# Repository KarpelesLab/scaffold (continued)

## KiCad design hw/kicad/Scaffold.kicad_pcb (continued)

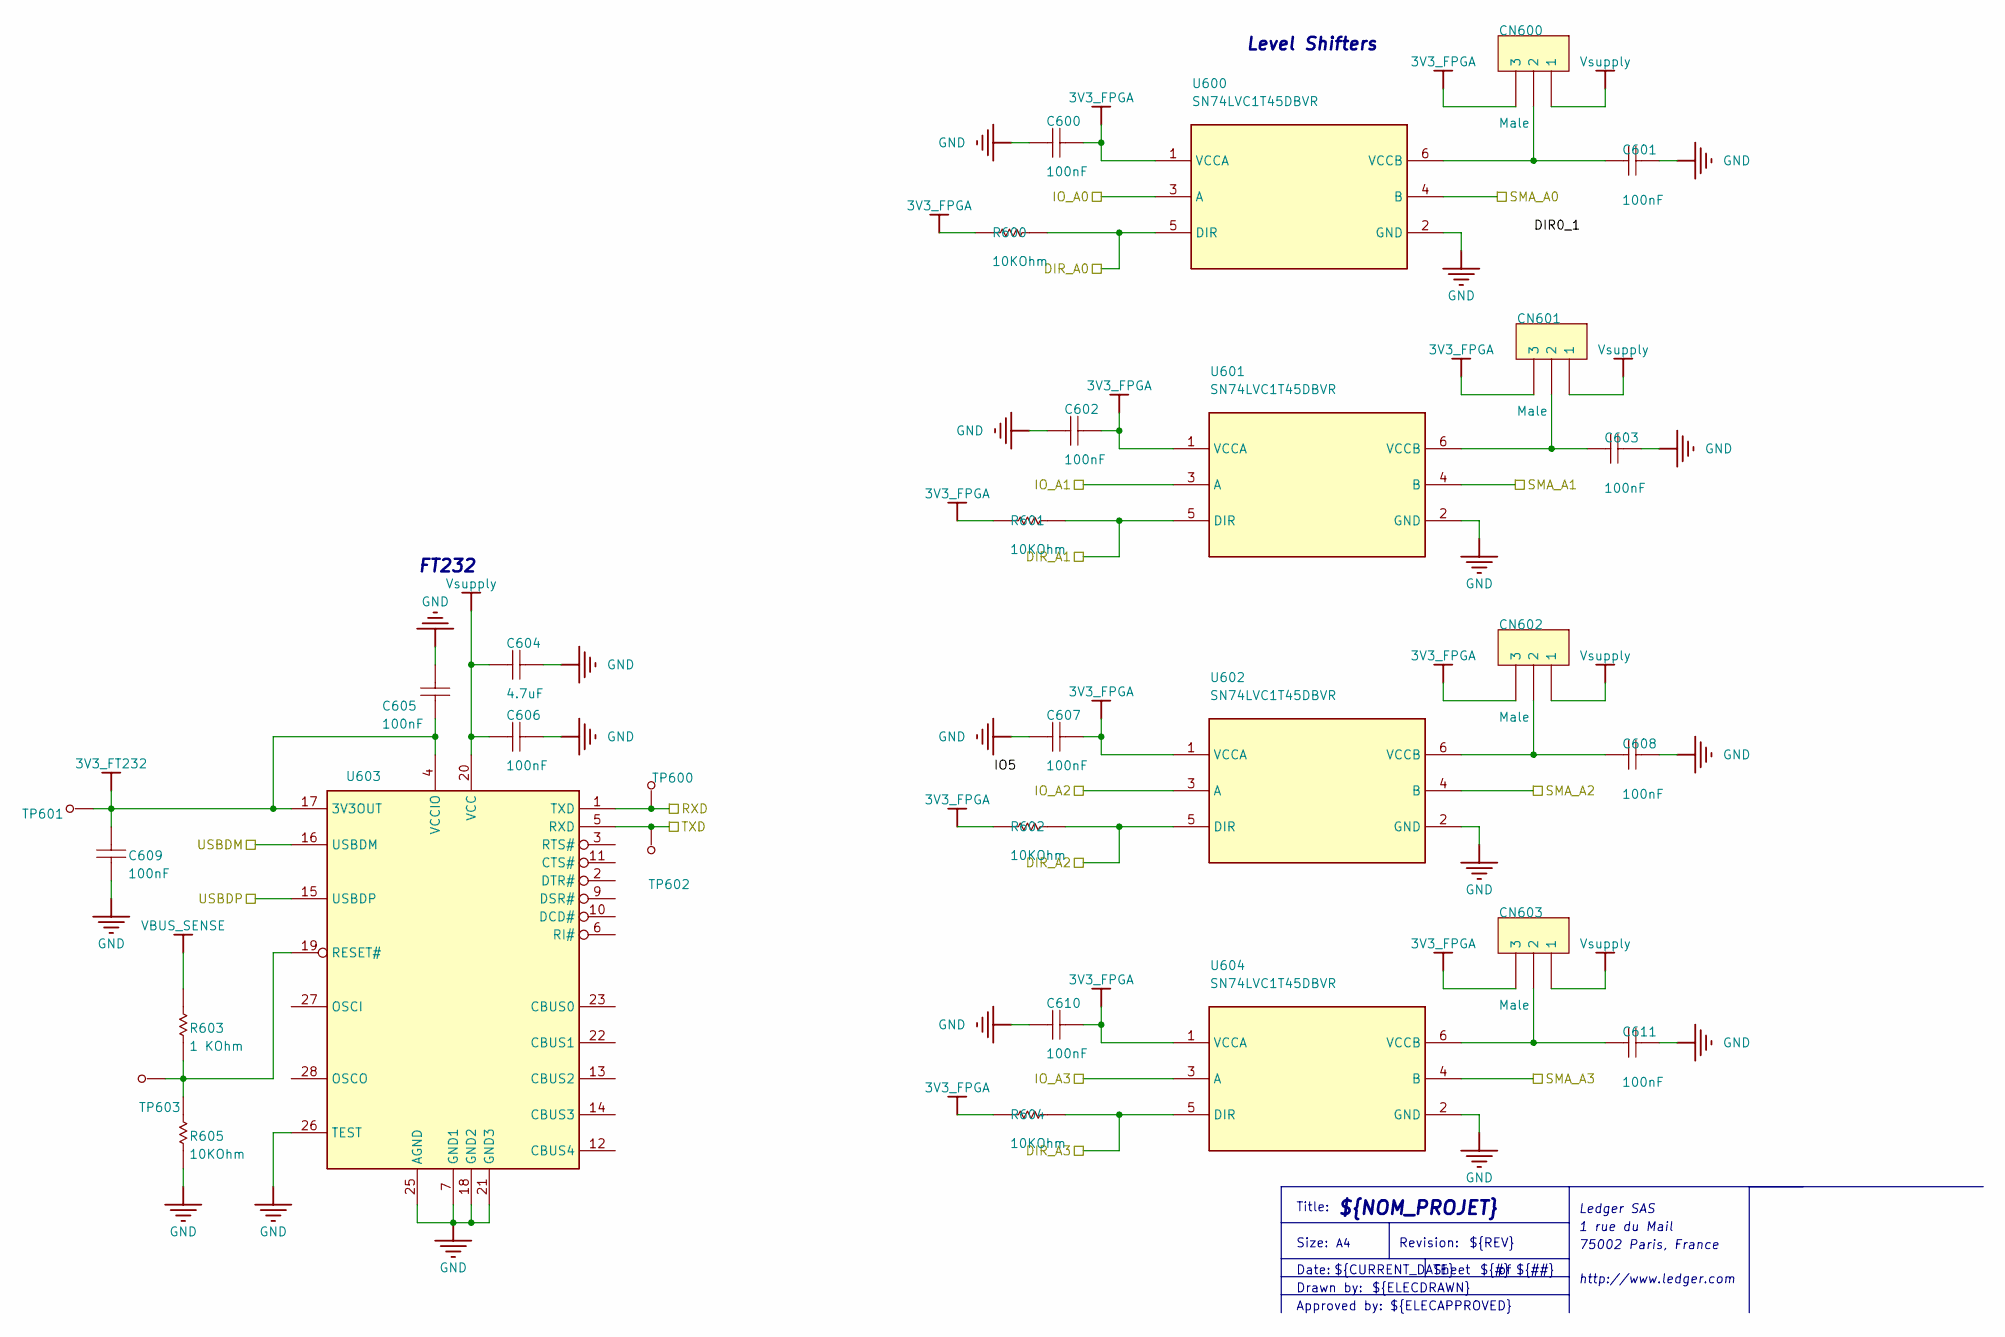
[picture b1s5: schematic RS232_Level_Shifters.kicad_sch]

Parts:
C600, C601, C602, C603, C605, C607, C608, C609, C610, C611: 100nF; CAP0603; TOLERANCE 10%; MANUFACTURER2 PN MCCA000159
C604: 4.7uF; CAP0603; TOLERANCE 10%; MANUFACTURER PN GRM188R61C475KE11
C606: 100nF; CAP0603; TOLERANCE 10%; MANUFACTURER PN 885012206046
CN600, CN601, CN602, CN603: Male; MOLEX_90120-0123; MANUFACTURER PN 90120-0123
R600, R601, R602, R604, R605: 10KOhm; RES0603; TOLERANCE 1%; MANUFACTURER PN RC0603FR-0710KL
R603: 1 KOhm; RES0603; TOLERANCE 1%; MANUFACTURER PN 0603WAF1001T5E
TP600, TP601, TP602, TP603: TP; TP_001
U600, U601, U602, U604: SN74LVC1T45DBVR; SOT95P280X145-6N; MANUFACTURER PN SN74LVC1T45DBVR
U603: IC - USB-to-UART 1-CH 256Byte FIFO - 5V - 28-Pin 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; SSOP28DB; MANUFACTURER PN FT232RL

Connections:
3V3_FPGA: C600.2, C602.2, C607.2, C610.2, CN600.3, CN601.3, CN602.3, CN603.3, R600.2, R601.2, R602.2, R604.2, U600.1 (VCCA), U601.1 (VCCA), U602.1 (VCCA), U604.1 (VCCA); also elsewhere on the board
3V3_FT232: C605.1, C609.1, TP601.1, U603.4 (VCCIO), U603.17 (3V3OUT)
/USBDM: U603.16 (USBDM); also elsewhere on the board
/USBDP: U603.15 (USBDP); also elsewhere on the board
/U_Connectors/IO_SMA0: U600.4 (B); also elsewhere on the board
/U_Connectors/IO_SMA1: U601.4 (B); also elsewhere on the board
/U_Connectors/IO_SMA2: U602.4 (B); also elsewhere on the board
/U_Connectors/IO_SMA3: U604.4 (B); also elsewhere on the board
/U_FPGA/DIR_A0: R600.1, U600.5 (DIR); also elsewhere on the board
/U_FPGA/DIR_A1: R601.1, U601.5 (DIR); also elsewhere on the board
/U_FPGA/DIR_A2: R602.1, U602.5 (DIR); also elsewhere on the board
/U_FPGA/DIR_A3: R604.1, U604.5 (DIR); also elsewhere on the board
/U_FPGA/IO_A0: U600.3 (A); also elsewhere on the board
/U_FPGA/IO_A1: U601.3 (A); also elsewhere on the board
/U_FPGA/IO_A2: U602.3 (A); also elsewhere on the board
/U_FPGA/IO_A3: U604.3 (A); also elsewhere on the board
/U_FPGA/RXD: TP600.1, U603.1 (TXD); also elsewhere on the board
/U_FPGA/TXD: TP602.1, U603.5 (RXD); also elsewhere on the board
GND: C600.1, C601.1, C602.1, C603.1, C604.2, C605.2, C606.2, C607.1, C608.1, C609.2, C610.1, C611.1, R605.1, U600.2 (GND), U601.2 (GND), U602.2 (GND), U603.7 (GND1), U603.18 (GND2), U603.21 (GND3), U603.25 (AGND), U603.26 (TEST), U604.2 (GND); also elsewhere on the board
unnamed: C601.2, CN600.2, U600.6 (VCCB)
unnamed: C603.2, CN601.2, U601.6 (VCCB)
unnamed: C608.2, CN602.2, U602.6 (VCCB)
unnamed: R603.1, R605.2, TP603.1, U603.19 (RESET#)
unnamed: C611.2, CN603.2, U604.6 (VCCB)
VBUS_SENSE: R603.2; also elsewhere on the board
Vsupply: C604.1, C606.1, CN600.1, CN601.1, CN602.1, CN603.1, U603.20 (VCC); also elsewhere on the board

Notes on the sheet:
Sheet
Title:
Approved by:
Drawn by:
Revision:
Date:
${CURRENT_DATE}
${#}
Ledger SAS
${REV}
Size:
${NOM_PROJET}
75002 Paris, France
${ELECAPPROVED}
FT232
${##}
http://www.ledger.com
1 rue du Mail
Level Shifters
${ELECDRAWN}

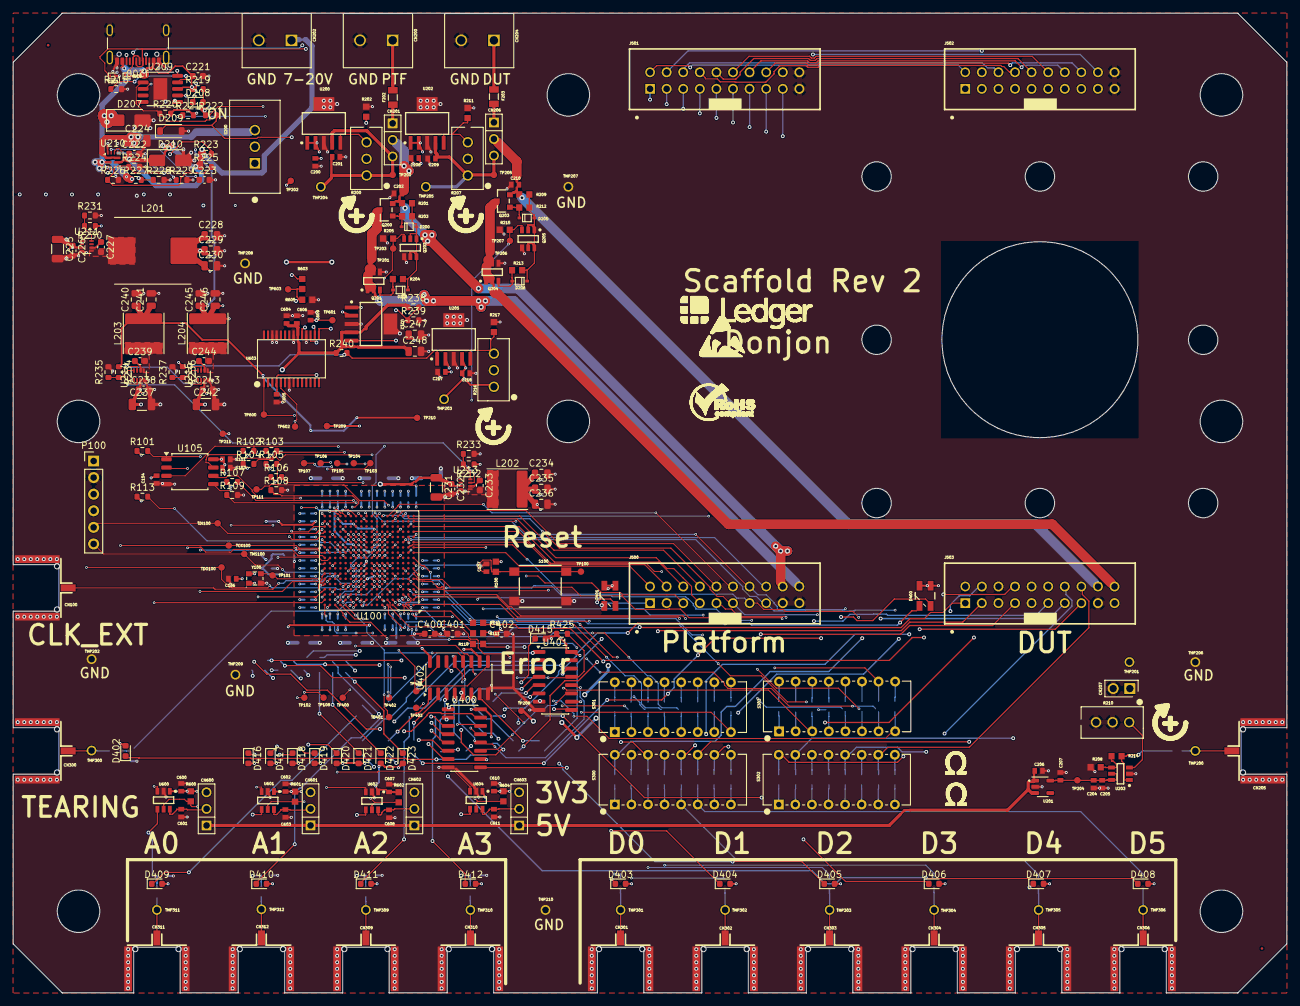
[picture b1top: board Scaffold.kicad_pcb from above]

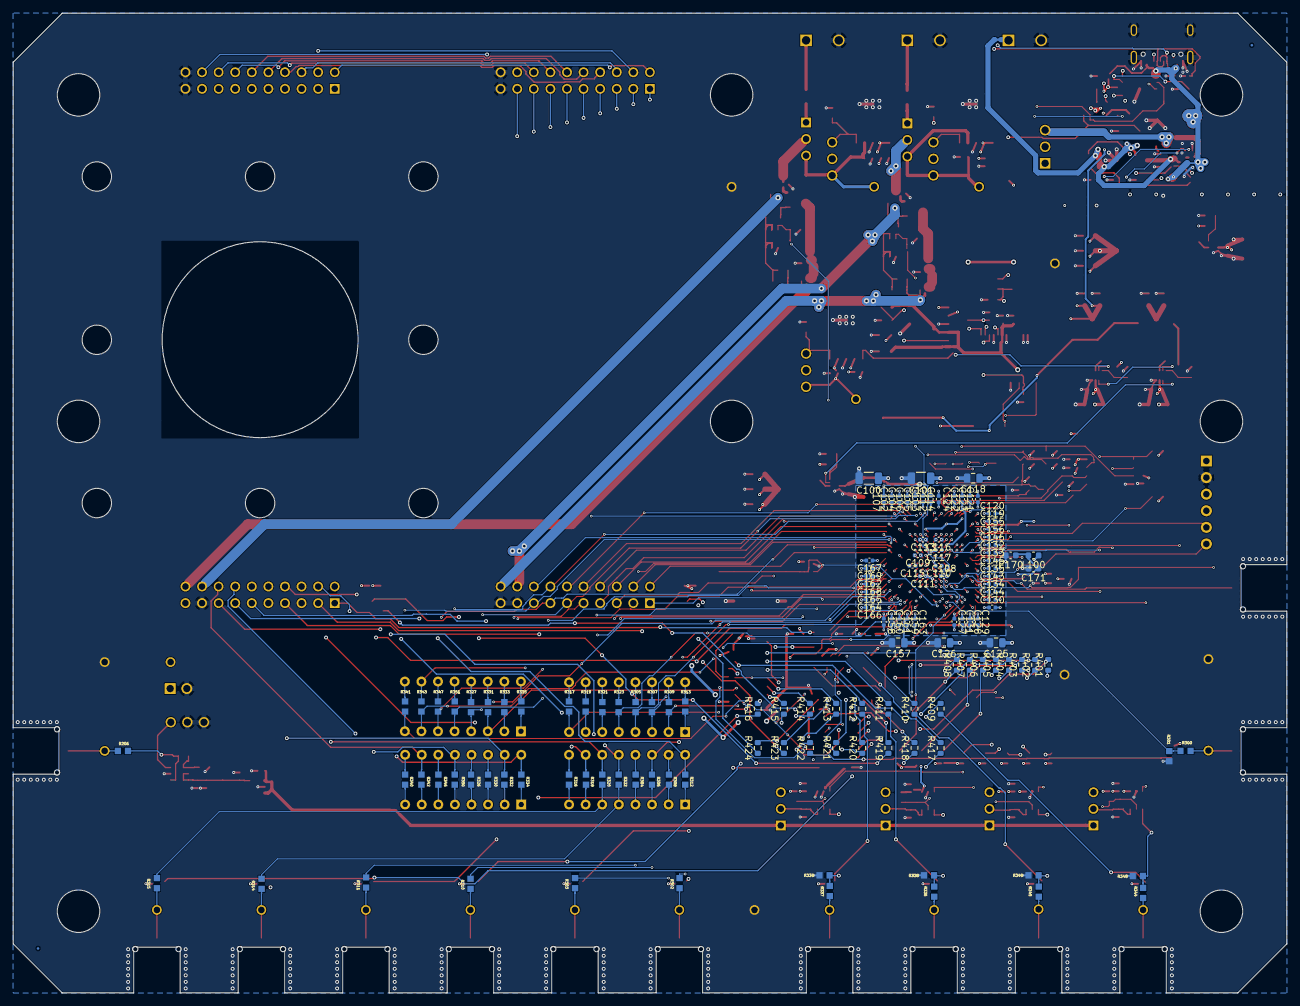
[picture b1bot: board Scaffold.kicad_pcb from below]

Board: 6 copper layers, 195.0 x 150.0 mm, 422 parts (133 on the bottom side), 252 nets.

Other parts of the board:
Logo1: Logo Ledger; logo_Ledger_new - Horizontale
Logo2: Logo ESD; LOGO ESD
Logo3: Logo ROHS
M1, M2, M3, M4: Mire; MIRE

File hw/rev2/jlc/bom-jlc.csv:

Comment,Designator,Footprint,LCSC
100uF 6.3V,"C100,C101",C_1206_3216Metric,C15008
4.7uF 10V,"C102,C103,C104,C105,C106,C107,C119,C120,C127,C128,C129,C130,C131,C158,C159,C160,C161",C_0402_1005Metric,C23733
470nF 10V,"C108,C109,C110,C111,C112,C113,C114,C115,C116,C117,C121,C122,C123,C124,C132,C133,C134,C135,C143,C144,C145,C146,C155,C156,C162,C163,C164,C165,C166,C167,C168,C169",C_0402_1005Metric,C47339
47uF 6.3V,"C118,C125,C126,C157",C_0805_2012Metric,C16780
100nF,"C136,C151,C153,C154,C205,C600,C601,C602,C603,C605,C606,C607,C608,C609,C610,C611",CAP0603,C14663
10uF,"C137,C200,C201,C202,C204,C208,C209,C210,C217,C218",CAP0603,C86277
1uF 50V,"C170,C221,C222",C_0603_1608Metric,C15849
100nF 50V,"C171,C226,C227,C232,C233,C238,C239,C243,C244,C400,C401,C402",C_0603_1608Metric,C14663
1uF,"C206,C207",CAP0603,C15849
10nF 50V,C223,C_0603_1608Metric,C57112
10uF 50V,"C224,C225,C231,C237,C242",C_1206_3216Metric,C13585
22uF 25V,"C228,C229,C230,C234,C235,C236,C240,C241,C245,C246",C_0805_2012Metric,C45783
10uF 25V,"C247,C248",C_0805_2012Metric,C15850
4.7uF,C604,CAP0603,C19666
Male,CN207,MOLEX_90120-0122,C3336192
BAT60J,"D200,D201,D205,D206",SOD323_A,C133103
ESDAXLC6-1BT2,"D203,D204",SOD882,C154523
SMAJ20A,"D207,D210",D_SMA,C115250
PD 12V OK (red),D208,LED_0603_1608Metric,C2286
BZT52C4V7,D209,D_SOD-123,C2116
LED RG,"D400,D401",PLCC-4_3528,C5872444
KT-0603Y,"D402,D403,D404,D405,D406,D407,D408,D409,D410,D411,D412,D416,D417,D418,D419,D420,D421,D422,D423",LED_0603_1608Metric,C2287
KT-0603R,D415,LED_0603_1608Metric,C2286
PTC - 1A - 0.5A - 6VDC,"F202,F203",FUSE_0805,C5220829
USB4105-GF-A,J200,USB_C_Receptacle_GCT_USB4105-xx-A_16P_TopMnt_Horizontal,C3020560
600R@100MHz,L100,L_0603_1608Metric,C1002
10uH,L201,L_CJiang_FXL1040,C475915
3.3uH,L202,L_Changjiang_FNR6045S,C168063
4.7uH,L203,L_Changjiang_FNR6045S,C168067
10uH,L204,L_Changjiang_FNR6045S,C168076
JTAG,P100,PinHeader_1x06_P2.54mm_Vertical,C492405
STR2P3LLH6 - SOT23,"Q200,Q203",SOT23,C3040112
STT6N3LLH6 - SOT23-6,"Q201,Q202,Q204,Q205",SOT95P280X145-6N,C3021100
47KOhm,R100,RES0603,C25819
10k,"R101,R102,R103,R220,R221,R224,R226,R228,R233,R425",R_0603_1608Metric,C25804
4.7k,"R104,R105,R222,R231",R_0603_1608Metric,C23162
330,"R106,R419,R420,R423,R424",R_0603_1608Metric,C23138
1k,"R107,R108,R109,R113",R_0603_1608Metric,C21190
10KOhm,"R110,R111,R112,R301,R305,R307,R309,R313,R317,R319,R321,R323,R327,R331,R333,R335,R338,R339,R341,R343,R347,R348,R349,R351,R600,R601,R602,R604,R605",RES0603,C25804
50 kOhms,"R200,R207,R216",POT_3296W,C83686
470Ohm,"R201,R209",RES0603,C23179
15KOhm,"R202,R211",RES0603,C22809
2Ohm,"R203,R204,R212,R213",RES0603,C22977
1K,"R205,R214,R215,R304,R306,R308,R312,R316,R318,R320,R322,R326,R330,R332,R334,R340,R342,R346,R350",RES0603,C21190
50 Ohm,R206,RES0603,C23185
100Ohm,R208,RES0603,C22775
100 Ohms,R210,POT_3296W,C83688
28KOhm,R217,RES0603,C22989
24k,R218,R_0603_1608Metric,C23352
2.2k,R219,R_0603_1608Metric,C4190
51k,R223,R_0603_1608Metric,C23196
200k,"R225,R227",R_0603_1608Metric,C25811
22k,R229,R_0603_1608Metric,C31850
30k,R230,R_0603_1608Metric,C22984
2.4k,R232,R_0603_1608Metric,C22940
15k,"R234,R237,R239",R_0603_1608Metric,C22809
12k,R235,R_0603_1608Metric,C22790
47k,"R236,R238",R_0603_1608Metric,C25819
100k,R240,R_0603_1608Metric,C25803
0 Ohm,"R300,R302,R303,R310,R311,R314,R315,R336,R337,R344,R345",RES0603,C21189
680,"R401,R402,R403,R404,R405,R406,R407,R408,R409,R410,R411,R412,R413,R414,R415,R416,R417,R418,R421,R422",R_0603_1608Metric,C23228
1 KOhm,R603,RES0603,C21190
Misc - DIP switch - 8 rows - TE connectivity - 1825057-7 -ADE0804,"S300,S301,S302,S303",SWDIP16_300X3.51,C266199
XC7A35T-1CSG324I,U100,Xilinx_CSG324,C1521726
W25Q128JVSIQ,U105,SOIC-8_5.3x5.3mm_P1.27mm,C97521
TL1963A,"U200,U202,U205,U212",SOT223-6,C86720
LDK130_33,U201,SOT95P280X145-5L30,C2969807
ADA4895-1,U203,SOT95P280X145-6N,C654294
CH224A,U209,SSOP-10-1EP_3.9x4.9mm_P1mm_EP2.1x3.3mm,C42459160
TPS2121RUXR,U210,Texas_VQFN-HR-12_2x2.5mm_P0.5mm,C485916
TPS62933PDRLR,"U211,U213,U214,U215",SOT-583-8,C5219254
74HC595D,"U400,U401,U402",SOIC-16_3.9x9.9mm_P1.27mm,C5947
SN74LVC1T45DBVR,"U600,U601,U602,U604",SOT95P280X145-6N,C7843
IC - USB-to-UART 1-CH 256Byte FIFO - 5V - 28-Pin SSOP,U603,SSOP28DB,C8690
Oscillator - 25MHz - 3.3V - HCMOS - ECS-2520S33-250-FN-TR,Y100,XTAL_2520,C2441341

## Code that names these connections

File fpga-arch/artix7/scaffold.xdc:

# Constraints for the Scaffold Rev 2 board (Artix-7 XC7A35T/XC7A100T, CSG324).
#
# PACKAGE_PIN assignments are generated from the schematic pin assignment
# (hw/rev2/fpga_pins.csv, see hw/rev2/tools/gen_fpga.py and gen_xdc.py).
# Bank voltages:
#   - banks 0/14/15/16: 3V3_FPGA (configuration, UART, LED driver, A0-A3, control)
#   - banks 34/35: VCC_IO_FPGA, adjustable 1.2 V to 3.3 V (DUT/platform I/Os)

# 25 MHz board oscillator.
create_clock -name clock -period 40.000 [get_ports clock]

# Configuration: 3.3 V bank 0, quad SPI flash, compressed bitstream.
set_property CFGBVS VCCO [current_design]
set_property CONFIG_VOLTAGE 3.3 [current_design]
set_property BITSTREAM.CONFIG.SPI_BUSWIDTH 4 [current_design]
set_property BITSTREAM.CONFIG.CONFIGRATE 33 [current_design]
set_property BITSTREAM.GENERAL.COMPRESS TRUE [current_design]

# Asynchronous inputs and outputs: no timing relationship with the system
# clock is required (the architecture synchronizes inputs internally).
set_false_path -from [get_ports {reset_n rx teardown io[*]}]
set_false_path -to [get_ports {tx leds_* io[*] io_dir[*] pull_d* power_*}]

# I/O standards. VCC_IO_FPGA is adjustable: LVCMOS33 is declared for the
# DUT/platform banks, the actual levels follow the bank supply.
set_property IOSTANDARD LVCMOS33 [get_ports *]
set_property PULLUP TRUE [get_ports reset_n]

# --- Pin assignments (generated by hw/rev2/tools/gen_xdc.py, do not edit) ---
set_property PACKAGE_PIN C15  [get_ports {clock}]   ;# CLK_25M, bank 15
set_property PACKAGE_PIN A11  [get_ports {reset_n}]   ;# RESET_N, bank 15
set_property PACKAGE_PIN L18  [get_ports {tx}]   ;# TXD, bank 14
set_property PACKAGE_PIN M18  [get_ports {rx}]   ;# RXD, bank 14
set_property PACKAGE_PIN A14  [get_ports {leds_lat}]   ;# LED_LE, bank 15
set_property PACKAGE_PIN A13  [get_ports {leds_sclk}]   ;# LED_CLK, bank 15
set_property PACKAGE_PIN A15  [get_ports {leds_sin}]   ;# LED_SDI, bank 15
set_property PACKAGE_PIN A18  [get_ports {leds_blank}]   ;# LED_/OE, bank 15
set_property PACKAGE_PIN B14  [get_ports {power_platform}]   ;# EN_VCC_PLATFORM, bank 15
set_property PACKAGE_PIN B16  [get_ports {power_dut}]   ;# EN_VCC_DUT, bank 15
set_property PACKAGE_PIN B13  [get_ports {teardown}]   ;# TEARING, bank 15
set_property PACKAGE_PIN B7   [get_ports {pull_d0}]   ;# PULL_D0, bank 35
set_property PACKAGE_PIN C2   [get_ports {pull_d1}]   ;# PULL_D1, bank 35
set_property PACKAGE_PIN D2   [get_ports {pull_d2}]   ;# PULL_D2, bank 35
set_property PACKAGE_PIN B18  [get_ports {io[0]}]   ;# IO_A0, bank 15
set_property PACKAGE_PIN G18  [get_ports {io_dir[0]}]   ;# DIR_A0, bank 15
set_property PACKAGE_PIN D18  [get_ports {io[1]}]   ;# IO_A1, bank 15
set_property PACKAGE_PIN J18  [get_ports {io_dir[1]}]   ;# DIR_A1, bank 15
set_property PACKAGE_PIN E18  [get_ports {io[2]}]   ;# IO_A2, bank 15
set_property PACKAGE_PIN B11  [get_ports {io_dir[2]}]   ;# DIR_A2, bank 15
set_property PACKAGE_PIN F18  [get_ports {io[3]}]   ;# IO_A3, bank 15
set_property PACKAGE_PIN B12  [get_ports {io_dir[3]}]   ;# DIR_A3, bank 15
set_property PACKAGE_PIN A1   [get_ports {io[4]}]   ;# IO0_DUT, bank 35
set_property PACKAGE_PIN L1   [get_ports {io[20]}]   ;# IO0_PLAT, bank 34
set_property PACKAGE_PIN A3   [get_ports {io[5]}]   ;# IO1_DUT, bank 35
set_property PACKAGE_PIN M1   [get_ports {io[21]}]   ;# IO1_PLAT, bank 34
set_property PACKAGE_PIN A4   [get_ports {io[6]}]   ;# IO2_DUT, bank 35
set_property PACKAGE_PIN N1   [get_ports {io[22]}]   ;# IO2_PLAT, bank 34
set_property PACKAGE_PIN A5   [get_ports {io[7]}]   ;# IO3_DUT, bank 35
set_property PACKAGE_PIN R1   [get_ports {io[23]}]   ;# IO3_PLAT, bank 34
set_property PACKAGE_PIN A6   [get_ports {io[8]}]   ;# IO4_DUT, bank 35
set_property PACKAGE_PIN T1   [get_ports {io[24]}]   ;# IO4_PLAT, bank 34
set_property PACKAGE_PIN B1   [get_ports {io[9]}]   ;# IO5_DUT, bank 35
set_property PACKAGE_PIN U1   [get_ports {io[25]}]   ;# IO5_PLAT, bank 34
set_property PACKAGE_PIN C1   [get_ports {io[10]}]   ;# IO6_DUT, bank 35
set_property PACKAGE_PIN V1   [get_ports {io[26]}]   ;# IO6_PLAT, bank 34
set_property PACKAGE_PIN E1   [get_ports {io[11]}]   ;# IO7_DUT, bank 35
set_property PACKAGE_PIN V2   [get_ports {io[27]}]   ;# IO7_PLAT, bank 34
set_property PACKAGE_PIN F1   [get_ports {io[12]}]   ;# IO8_DUT, bank 35
set_property PACKAGE_PIN V4   [get_ports {io[28]}]   ;# IO8_PLAT, bank 34
set_property PACKAGE_PIN G1   [get_ports {io[13]}]   ;# IO9_DUT, bank 35
set_property PACKAGE_PIN V5   [get_ports {io[29]}]   ;# IO9_PLAT, bank 34
set_property PACKAGE_PIN H1   [get_ports {io[14]}]   ;# IO10_DUT, bank 35
set_property PACKAGE_PIN V6   [get_ports {io[30]}]   ;# IO10_PLAT, bank 34
set_property PACKAGE_PIN K1   [get_ports {io[15]}]   ;# IO11_DUT, bank 35
set_property PACKAGE_PIN V7   [get_ports {io[31]}]   ;# IO11_PLAT, bank 34
set_property PACKAGE_PIN B2   [get_ports {io[16]}]   ;# IO12_DUT, bank 35
set_property PACKAGE_PIN V9   [get_ports {io[32]}]   ;# IO12_PLAT, bank 34
set_property PACKAGE_PIN B3   [get_ports {io[17]}]   ;# IO13_DUT, bank 35
set_property PACKAGE_PIN M2   [get_ports {io[33]}]   ;# IO13_PLAT, bank 34
set_property PACKAGE_PIN B4   [get_ports {io[18]}]   ;# IO14_DUT, bank 35
set_property PACKAGE_PIN N2   [get_ports {io[34]}]   ;# IO14_PLAT, bank 34
set_property PACKAGE_PIN B6   [get_ports {io[19]}]   ;# IO15_DUT, bank 35
set_property PACKAGE_PIN P2   [get_ports {io[35]}]   ;# IO15_PLAT, bank 34
# Board nets wired to the FPGA but not used by the gateware: CLK_EXT=G16, FLASH_CS=L13, FLASH_IO0=K17, FLASH_IO1=K18, FLASH_IO2=L14, FLASH_IO3=M14, LED_SDO=A16, PD_SCL=P18, PD_SDA=R18, PUDC_B=L15, SPARE_0=T18, SPARE_1=U18, SPARE_2=V10, SPARE_3=V11, SPARE_4=V12, SPARE_5=V14, SPARE_6=V15
# --- End of generated pin assignments ---

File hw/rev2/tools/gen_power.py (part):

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props_ldo = {k: v for k, v in base.parts["U200"]["props"].items() if k not in base.SKIP_PROPS}
g.add("U212", sym_ldo, {"1": "VPRE", "2": "VPRE", "3": "GND", "4": "Vsupply", "5": "VSUP_ADJ", "6": "GND"},
      value="TL1963A", footprint=base.parts["U200"]["props"]["Footprint"], fields=dict(props_ldo, LCSC="C86720"))
R(g, "R%d" % rnum, "47k", "Vsupply", "VSUP_ADJ"); rnum += 1
R(g, "R%d" % rnum, "15k", "VSUP_ADJ", "GND"); rnum += 1
C(g, "C%d" % cnum, "10uF/25V", "VPRE"); cnum += 1
C(g, "C%d" % cnum, "10uF/25V", "Vsupply"); cnum += 1

g = Grid(sheet, X2, g.bottom() + 30, 250,
         "VCC_IO_FPGA 1.21-3.37 V (banks 34/35), enabled after 3V3_FPGA is good")
base.place(g, "U205", {"1": "PG_3V3", "2": "VPRE", "3": "GND", "4": "VCC_IO_FPGA", "5": "VCCIO_ADJ", "6": "GND"},
           fields={"LCSC": "C86720"})
R(g, "R%d" % rnum, "100k", "Vsupply", "PG_3V3"); rnum += 1
base.place(g, "R216", {"1": "VCC_IO_FPGA", "2": "VCCIO_ADJ", "3": "VCCIO_ADJ"})
base.place(g, "R217", {"1": "GND", "2": "VCCIO_ADJ"})
base.place(g, "C217", {"1": "GND", "2": "VPRE"})
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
